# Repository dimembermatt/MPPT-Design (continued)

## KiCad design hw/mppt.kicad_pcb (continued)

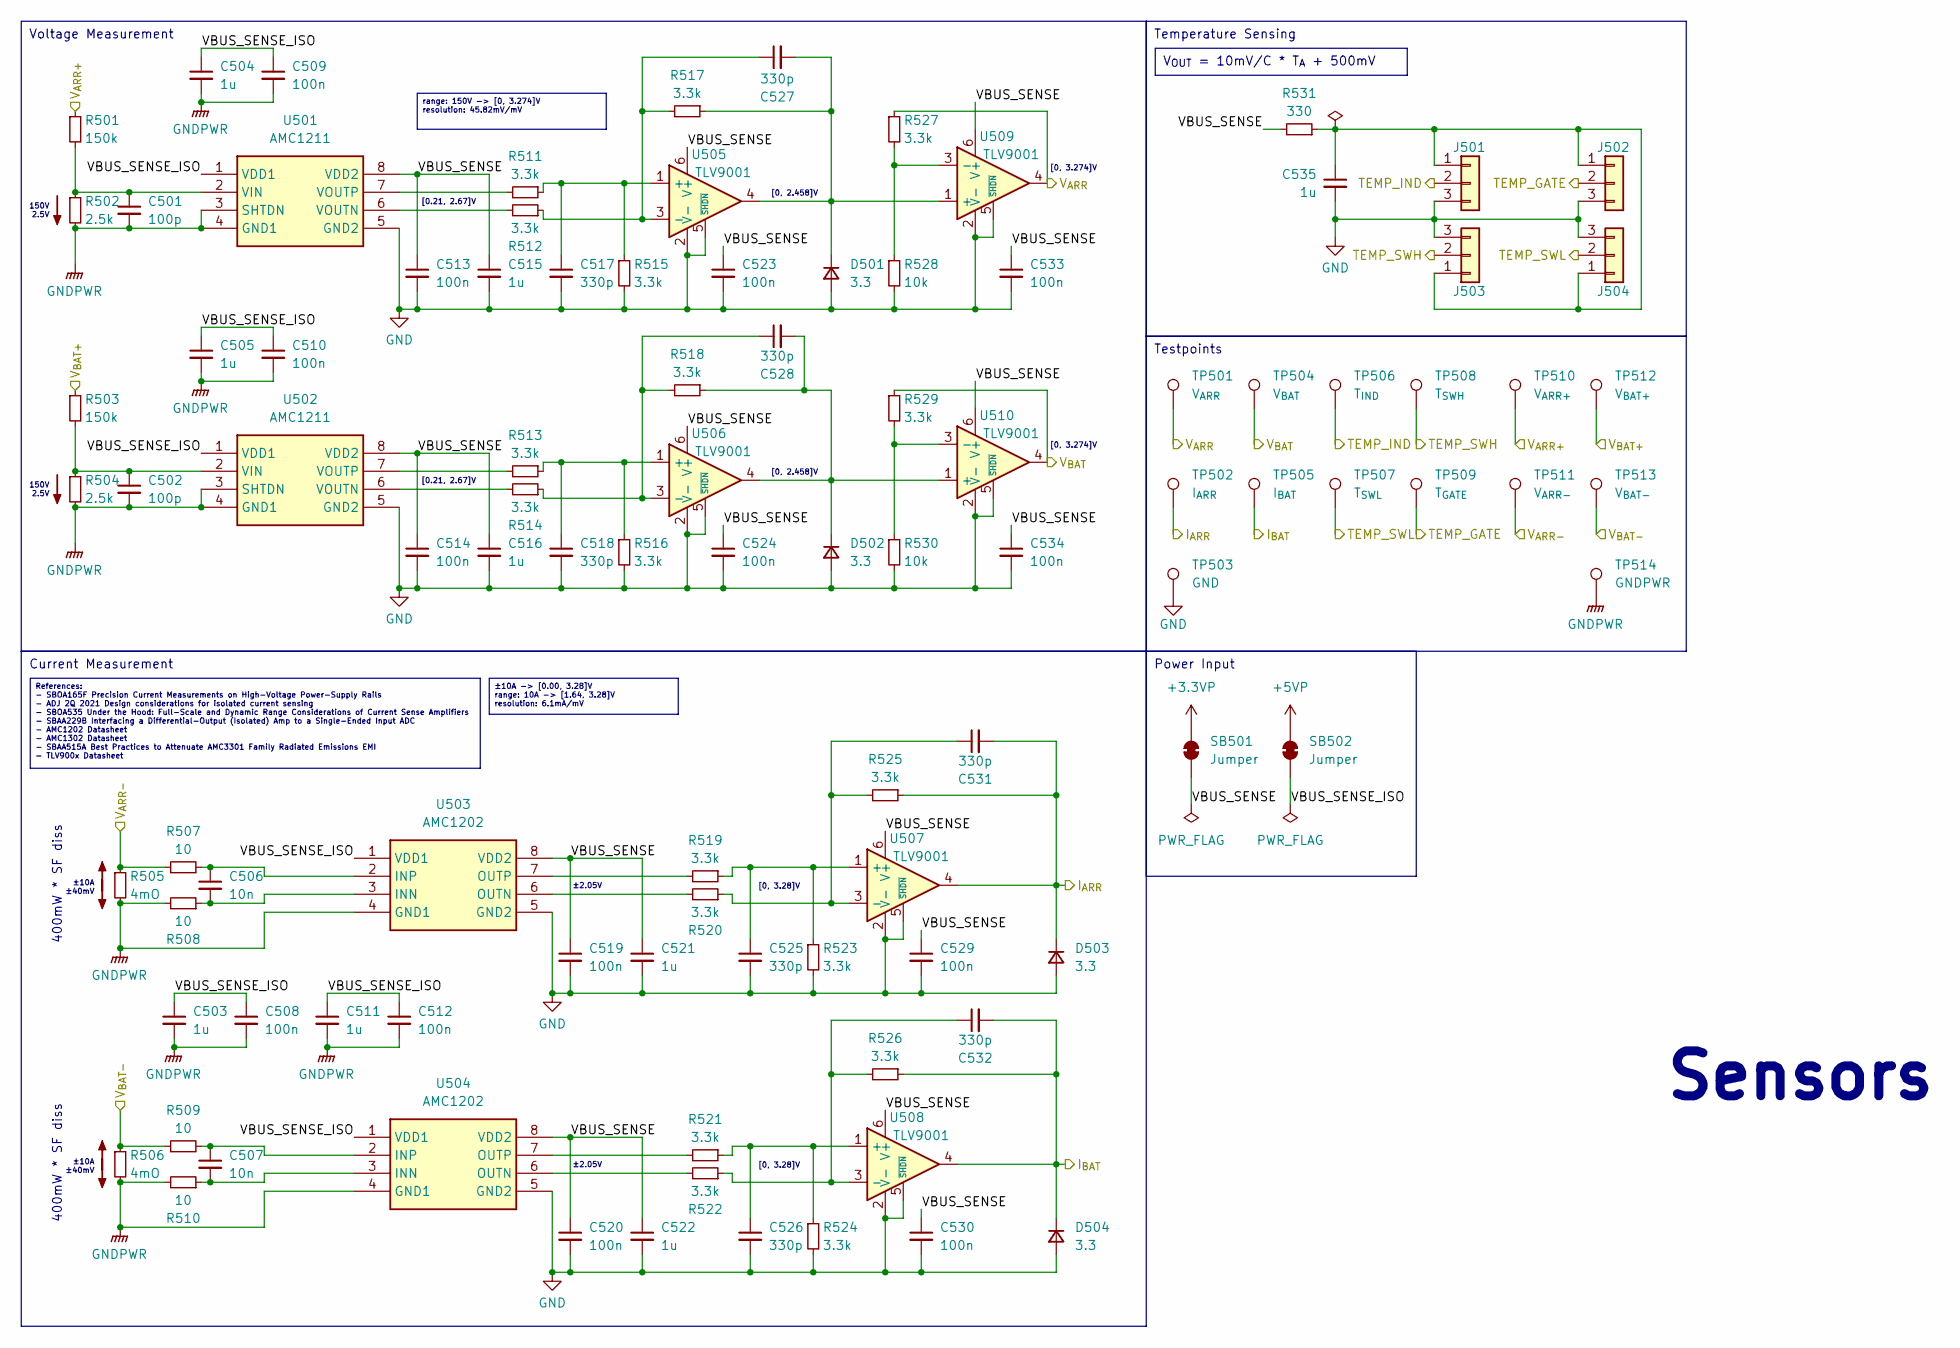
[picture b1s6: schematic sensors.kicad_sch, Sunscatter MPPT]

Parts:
C501, C502: 100p; R_0402_1005Metric; LCSC Part # C472445
C503, C504, C505, C511, C515, C516, C521, C522, C535: 1u; R_0402_1005Metric; LCSC Part # C307454
C506, C507: 10n; R_0402_1005Metric; LCSC Part # C307330
C508, C509, C510, C512, C513, C514, C519, C520, C523, C524, C529, C530, C533, C534: 100n; R_0402_1005Metric; LCSC Part # C307331
C517, C518, C525, C526, C527, C528, C531, C532: 330p; R_0402_1005Metric; LCSC Part # C307432
D501, D502, D503, D504: 3.3; D_SOD-123
J501, J502, J503, J504: Conn_01x03; JST_PH_B3B-PH-K_1x03_P2.00mm_Vertical
R501, R503: 150k; R_0805_2012Metric; LCSC Part # C17470
R502, R504: 2.5k; R_0805_2012Metric; LCSC Part # C5713447
R505, R506: 4mO; R_2512_6332Metric; LCSC Part # C2941090
R507, R508, R509, R510: 10; R_0402_1005Metric; LCSC Part # C25077
R511, R512, R513, R514, R515, R516, R517, R518, R519, R520, R521, R522, R523, R524, R525, R526, R527, R529: 3.3k; R_0402_1005Metric; LCSC Part # C25890
R528, R530: 10k; R_0402_1005Metric; LCSC Part # C25744
R531: 330; R_0402_1005Metric; LCSC Part # C25105
SB501, SB502: Jumper; SolderJumper-2_P1.3mm_Open_TrianglePad1.0x1.5mm
TP501: V_{ARR}; TestPoint_Pad_D1.5mm
TP502: I_{ARR}; TestPoint_Pad_D1.5mm
TP503: GND; TestPoint_Pad_D1.5mm
TP504: V_{BAT}; TestPoint_Pad_D1.5mm
TP505: I_{BAT}; TestPoint_Pad_D1.5mm
TP506: T_{IND}; TestPoint_Pad_D1.5mm
TP507: T_{SWL}; TestPoint_Pad_D1.5mm
TP508: T_{SWH}; TestPoint_Pad_D1.5mm
TP509: T_{GATE}; TestPoint_Pad_D1.5mm
TP510: V_{ARR+}; TestPoint_Pad_D1.5mm
TP511: V_{ARR-}; TestPoint_Pad_D1.5mm
TP512: V_{BAT+}; TestPoint_Pad_D1.5mm
TP513: V_{BAT-}; TestPoint_Pad_D1.5mm
TP514: GNDPWR; TestPoint_Pad_D1.5mm
U501, U502: AMC1211; ti_AMC1211_DWV
U503, U504: AMC1202; ti_AMC1202_DWV
U505, U506, U507, U508, U509, U510: TLV9001; SOT-363_SC-70-6

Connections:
+3.3VP: SB501.2 (B); also elsewhere on the board
+5VP: SB502.2 (B); also elsewhere on the board
/I_{ARR}: C531.2, D503.1 (K), R525.1, TP502.1, U507.4; also elsewhere on the board
/I_{BAT}: C532.2, D504.1 (K), R526.1, TP505.1, U508.4; also elsewhere on the board
/TEMP_GATE: J502.2, TP509.1; also elsewhere on the board
/TEMP_IND: J501.2, TP506.1; also elsewhere on the board
/TEMP_SWH: J503.2, TP508.1; also elsewhere on the board
/TEMP_SWL: J504.2, TP507.1; also elsewhere on the board
/V_{ARR+}: R501.1, TP510.1; also elsewhere on the board
/V_{ARR-}: R505.1, R507.1, TP511.1; also elsewhere on the board
/V_{ARR}: R527.1, TP501.1, U509.4; also elsewhere on the board
/V_{BAT+}: R503.1, TP512.1; also elsewhere on the board
/V_{BAT-}: R506.1, R509.1, TP513.1; also elsewhere on the board
/V_{BAT}: R529.1, TP504.1, U510.4; also elsewhere on the board
/sensors/VBUS_SENSE: C513.1, C514.1, C515.1, C516.1, C519.1, C520.1, C521.1, C522.1, C523.1, C524.1, C529.1, C530.1, C533.1, C534.1, R531.2, SB501.1 (A), U501.8 (VDD2), U502.8 (VDD2), U503.8 (VDD2), U504.8 (VDD2), U505.6 (V+), U506.6 (V+), U507.6 (V+), U508.6 (V+), U509.6 (V+), U510.6 (V+)
/sensors/VBUS_SENSE_ISO: C503.1, C504.1, C505.1, C508.1, C509.1, C510.1, C511.1, C512.1, SB502.1 (A), U501.1 (VDD1), U502.1 (VDD1), U503.1 (VDD1), U504.1 (VDD1)
GND: C513.2, C514.2, C515.2, C516.2, C517.2, C518.2, C519.2, C520.2, C521.2, C522.2, C523.2, C524.2, C525.2, C526.2, C529.2, C530.2, C533.2, C534.2, C535.2, D501.2 (A), D502.2 (A), D503.2 (A), D504.2 (A), J501.3, J502.3, J503.3, J504.3, R515.2, R516.2, R523.2, R524.2, R528.2, R530.2, TP503.1, U501.5 (GND2), U502.5 (GND2), U503.5 (GND2), U504.5 (GND2), U505.2 (V-), U505.5 (~SHDN), U506.2 (V-), U506.5 (~SHDN), U507.2 (V-), U507.5 (~SHDN), U508.2 (V-), U508.5 (~SHDN), U509.2 (V-), U509.5 (~SHDN), U510.2 (V-), U510.5 (~SHDN); also elsewhere on the board
GNDPWR: C501.2, C502.2, C503.2, C504.2, C505.2, C508.2, C509.2, C510.2, C511.2, C512.2, R502.2, R504.2, R505.2, R506.2, R508.2, R510.2, TP514.1, U501.3 (SHTDN), U501.4 (GND1), U502.3 (SHTDN), U502.4 (GND1), U503.4 (GND1), U504.4 (GND1); also elsewhere on the board
unnamed: C527.2, D501.1 (K), R517.1, U505.4, U509.1 (+)
unnamed: C528.2, D502.1 (K), R518.1, U506.4, U510.1 (+)
unnamed: C535.1, J501.1, J502.1, J503.1, J504.1, R531.1
unnamed: C501.1, R501.2, R502.1, U501.2 (VIN)
unnamed: R512.2, U501.6 (VOUTN)
unnamed: R511.2, U501.7 (VOUTP)
unnamed: C502.1, R503.2, R504.1, U502.2 (VIN)
unnamed: R514.2, U502.6 (VOUTN)
unnamed: R513.2, U502.7 (VOUTP)
unnamed: C506.2, R508.1, U503.3 (INN)
unnamed: C506.1, R507.2, U503.2 (INP)
unnamed: R520.2, U503.6 (OUTN)
unnamed: R519.2, U503.7 (OUTP)
unnamed: C507.2, R510.1, U504.3 (INN)
unnamed: C507.1, R509.2, U504.2 (INP)
unnamed: R522.2, U504.6 (OUTN)
unnamed: R521.2, U504.7 (OUTP)
unnamed: C517.1, R511.1, R515.1, U505.1 (+)
unnamed: C527.1, R512.1, R517.2, U505.3 (-)
unnamed: C518.1, R513.1, R516.1, U506.1 (+)
unnamed: C528.1, R514.1, R518.2, U506.3 (-)
unnamed: C525.1, R519.1, R523.1, U507.1 (+)
unnamed: C531.1, R520.1, R525.2, U507.3 (-)
unnamed: C526.1, R521.1, R524.1, U508.1 (+)
unnamed: C532.1, R522.1, R526.2, U508.3 (-)
unnamed: R527.2, R528.1, U509.3 (-)
unnamed: R529.2, R530.1, U510.3 (-)

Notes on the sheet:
References: - SBOA165F Precision Current Measurements on High-Voltage Power-Supply Rails - ADJ 2Q 2021 Design considerations for isolated current sensing - SBOA535 Under the Hood: Full-Scale and Dynamic Range Considerations of Current Sense Amplifiers - SBAA229B Interfacing a Differential-Output (I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
V_{OUT} = 10mV/C * T_{A} + 500mV
Temperature Sensing
range: 150V -> [0, 3.274]V resolution: 45.82mV/mV
Current Measurement
Power Input
±10A -> [0.00, 3.28]V range: 10A -> [1.64, 3.28]V resolution: 6.1mA/mV
Testpoints
Voltage Measurement
[0.21, 2.67]V
150V 2.5V
[0, 3.28]V
[0, 2.458]V
±2.05V
[0, 3.274]V
Sensors
±10A ±40mV
400mW * SF diss

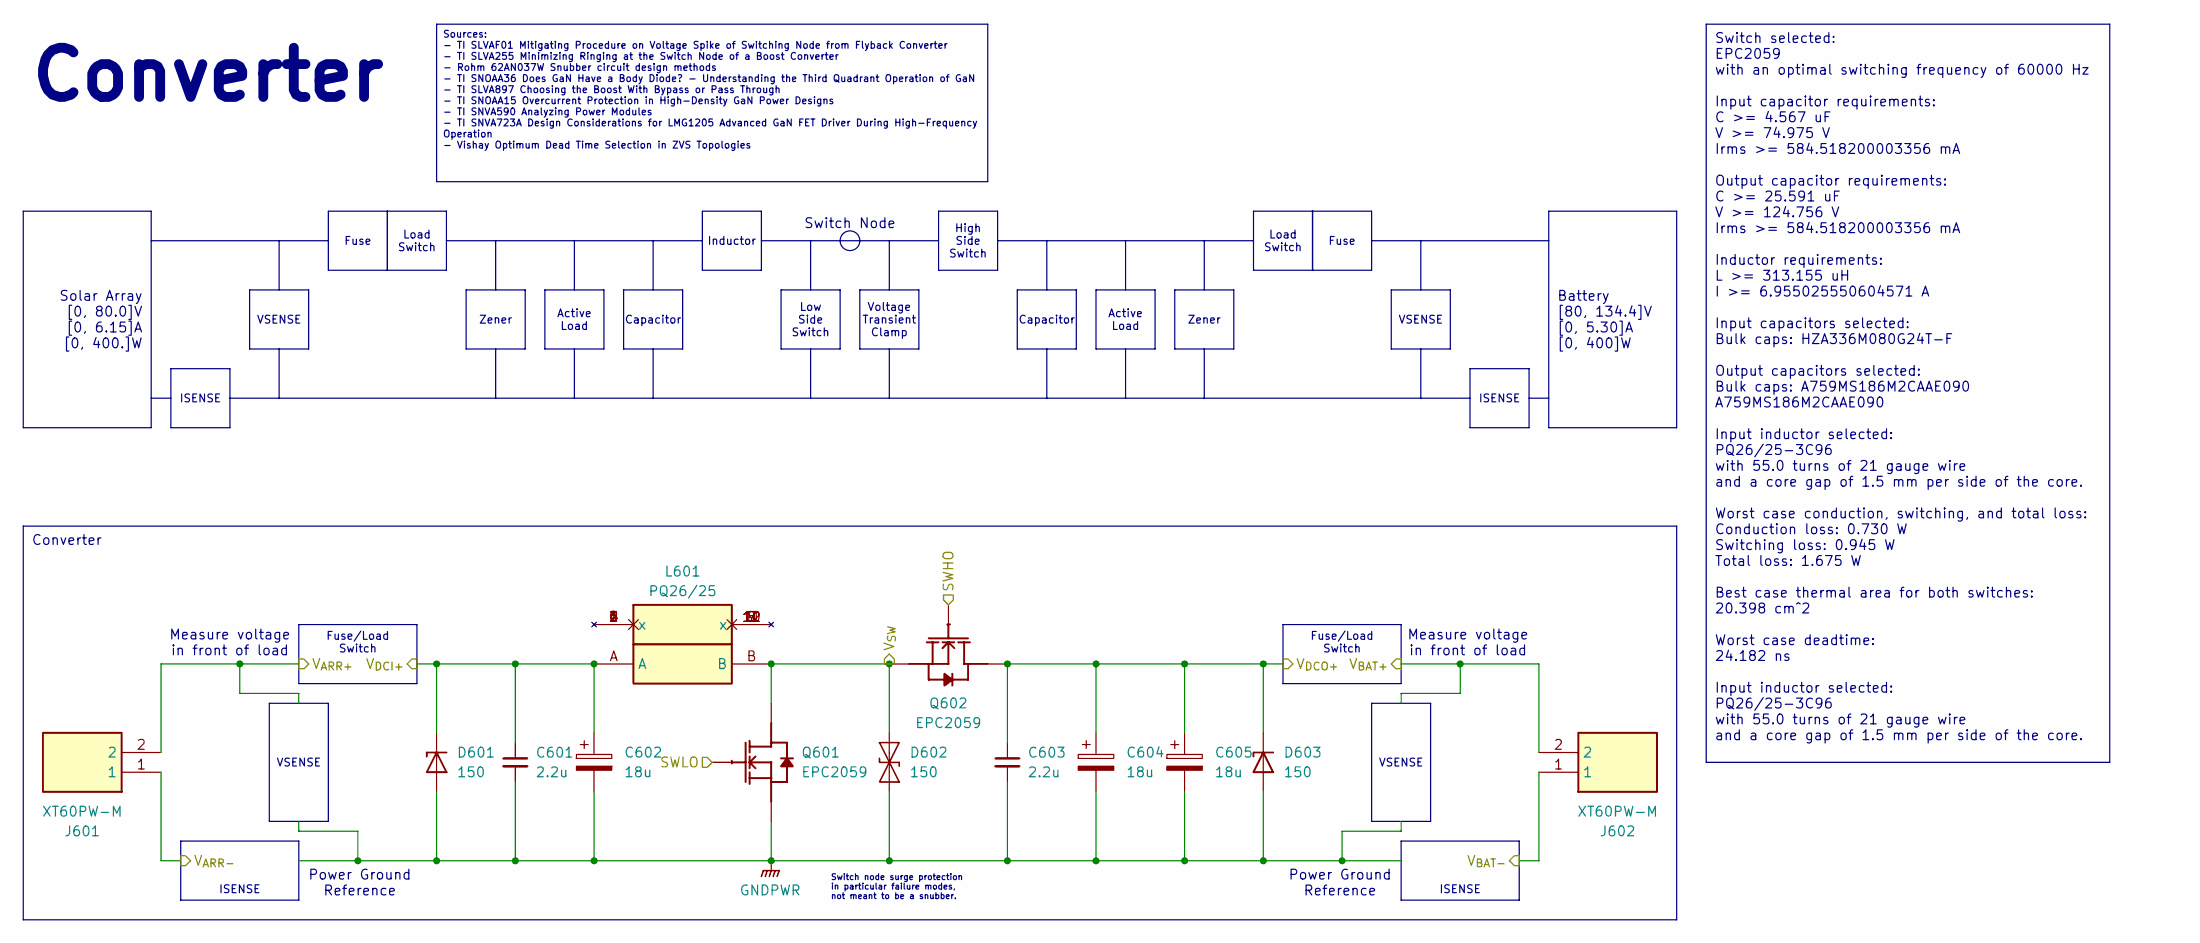
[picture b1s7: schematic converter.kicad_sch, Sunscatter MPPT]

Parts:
C601, C603: 2.2u; C_2220_5750Metric_Pad1.97x5.40mm_HandSolder
C602, C604, C605: 18u; C_Radial_D10.0mm_H16.0mm_P5.00mm
D601, D602, D603: 150; D_SMA
J601, J602: XT60PW-M; amass_XT60PW_M; LCSC Part # C98732
L601: PQ26/25; ferroxcube_CSV-PQ26_25-1S-12P-ZF
Q601, Q602: EPC2059; epc_EPC2059

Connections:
/SWHO: Q602.1 (G); also elsewhere on the board
/SWLO: Q601.1 (G); also elsewhere on the board
/V_{ARR+}: J601.2; also elsewhere on the board
/V_{ARR-}: J601.1; also elsewhere on the board
/V_{BAT+}: J602.2; also elsewhere on the board
/V_{BAT-}: J602.1; also elsewhere on the board
/V_{DCI+}: C601.1, C602.1, D601.1 (K), L601.A; also elsewhere on the board
/V_{DCO+}: C603.1, C604.1, C605.1, D603.1 (K), Q602.3 (D), Q602.5 (D); also elsewhere on the board
/V_{SW}: D602.2 (A2), L601.B, Q601.3 (D), Q601.5 (D), Q602.2 (S), Q602.4 (S), Q602.6 (S); also elsewhere on the board
GNDPWR: C601.2, C602.2, C603.2, C604.2, C605.2, D601.2 (A), D602.1 (A1), D603.2 (A), Q601.2 (S), Q601.4 (S), Q601.6 (S); also elsewhere on the board

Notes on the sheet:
Voltage Transient Clamp
Zener
VSENSE
Capacitor
ISENSE
Fuse/Load Switch
Low Side Switch
Converter
Solar Array [0, 80.0]V [0, 6.15]A [0, 400.]W
High Side Switch
Switch selected: EPC2059 with an optimal switching frequency of 60000 Hz Input capacitor requirements: C >= 4.567 uF V >= 74.975 V Irms >= 584.518200003356 mA Output capacitor requirements: C >= 25.591 uF V >= 124.756 V Irms >= 584.518200003356 mA Inductor requirements: L >= 313.155 uH I >= 6.95502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
Load Switch
Fuse
Active Load
Sources: - TI SLVAF01 Mitigating Procedure on Voltage Spike of Switching Node from Flyback Converter - TI SLVA255 Minimizing Ringing at the Switch Node of a Boost Converter - Rohm 62AN037W Snubber circuit design methods - TI SNOAA36 Does GaN Have a Body Diode? - Understanding the Third Quadrant Ope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
Inductor
Battery [80, 134.4]V [0, 5.30]A [0, 400]W
Switch node surge protection in particular failure modes, not meant to be a snubber.
Measure voltage in front of load
Switch Node
Power Ground Reference

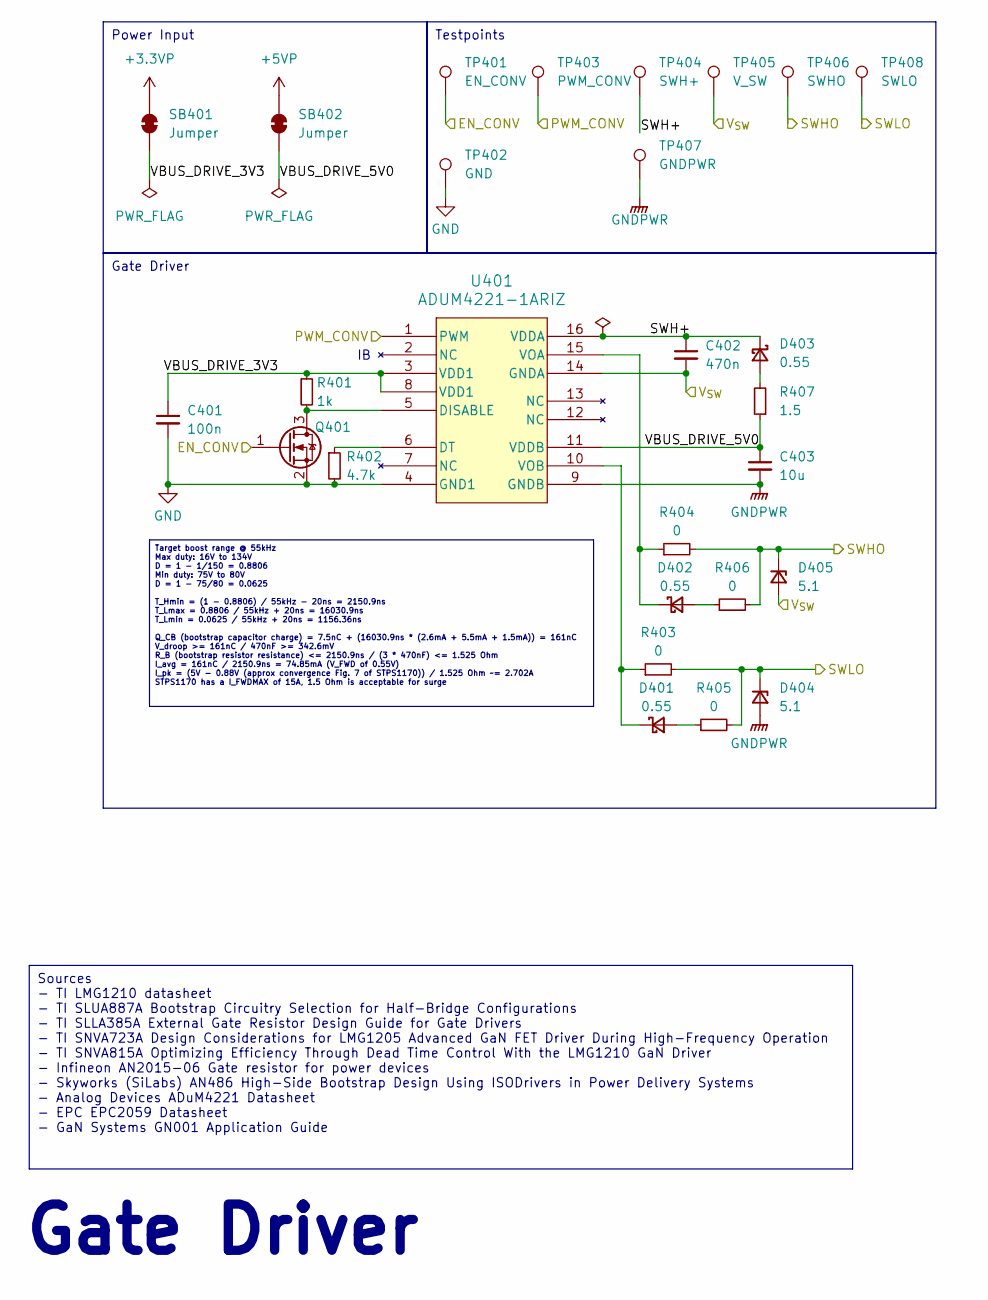
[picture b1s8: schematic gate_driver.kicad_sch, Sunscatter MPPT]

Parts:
C401: 100n; R_0402_1005Metric; LCSC Part # C307331
C402: 470n; R_0402_1005Metric; LCSC Part # C92361
C403: 10u; R_0805_2012Metric
D401, D402, D403: 0.55; stm_STPS1170AF
D404, D405: 5.1; D_SOD-123
Q401: BSS127S; SOT-23
R401: 1k; R_0402_1005Metric; LCSC Part # C11702
R402: 4.7k; R_0402_1005Metric; LCSC Part # C25900
R403, R404, R405, R406: 0; R_0402_1005Metric
R407: 1.5; R_0402_1005Metric; LCSC Part # C270642
SB401, SB402: Jumper; SolderJumper-2_P1.3mm_Open_TrianglePad1.0x1.5mm
TP401: EN_CONV; TestPoint_Pad_D1.5mm
TP402: GND; TestPoint_Pad_D1.5mm
TP403: PWM_CONV; TestPoint_Pad_D1.5mm
TP404: SWH+; TestPoint_Pad_D1.5mm
TP405: V_SW; TestPoint_Pad_D1.5mm
TP406: SWHO; TestPoint_Pad_D1.5mm
TP407: GNDPWR; TestPoint_Pad_D1.5mm
TP408: SWLO; TestPoint_Pad_D1.5mm
U401: ADUM4221-1ARIZ; ad_ADUM5221_1ARIZ

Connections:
+3.3VP: SB401.2 (B); also elsewhere on the board
+5VP: SB402.2 (B); also elsewhere on the board
/EN_CONV: Q401.1 (G), TP401.1; also elsewhere on the board
/PWM_CONV: TP403.1, U401.1 (PWM); also elsewhere on the board
/SWHO: D405.1 (K), R404.2, R406.2, TP406.1; also elsewhere on the board
/SWLO: D404.1 (K), R403.2, R405.2, TP408.1; also elsewhere on the board
/V_{SW}: C402.2, D405.2 (A), TP405.1, U401.14 (GNDA); also elsewhere on the board
/gate_driver/SWH+: C402.1, D403.1 (K), TP404.1, U401.16 (VDDA)
/gate_driver/VBUS_DRIVE_3V3: C401.1, R401.1, SB401.1 (A), U401.3 (VDD1), U401.8 (VDD1)
/gate_driver/VBUS_DRIVE_5V0: C403.1, R407.1, SB402.1 (A), U401.11 (VDDB)
GND: C401.2, Q401.2 (S), R402.2, TP402.1, U401.4 (GND1); also elsewhere on the board
GNDPWR: C403.2, D404.2 (A), TP407.1, U401.9 (GNDB); also elsewhere on the board
unnamed: D401.2 (A), R405.1
unnamed: D401.1 (K), R403.1, U401.10 (VOB)
unnamed: D402.2 (A), R406.1
unnamed: D402.1 (K), R404.1, U401.15 (VOA)
unnamed: D403.2 (A), R407.2
unnamed: Q401.3 (D), R401.2, U401.5 (DISABLE)
unnamed: R402.1, U401.6 (DT)

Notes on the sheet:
Power Input
Gate Driver
Sources - TI LMG1210 datasheet - TI SLUA887A Bootstrap Circuitry Selection for Half-Bridge Configurations - TI SLLA385A External Gate Resistor Design Guide for Gate Drivers - TI SNVA723A Design Considerations for LMG1205 Advanced GaN FET Driver During High-Frequency Operation - TI SNVA815A Optimizi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
Target boost range @ 55kHz Max duty: 16V to 134V D = 1 - 1/150 = 0.8806 Min duty: 75V to 80V D = 1 - 75/80 = 0.0625 T_Hmin = (1 - 0.8806) / 55kHz - 20ns = 2150.9ns T_Lmax = 0.8806 / 55kHz + 20ns = 16030.9ns T_Lmin = 0.0625 / 55kHz + 20ns = 1156.36ns Q_CB (bootstrap capacitor charge) = 7.5nC + (1603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
Testpoints

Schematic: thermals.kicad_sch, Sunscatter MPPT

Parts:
C801: 22u; R_0805_2012Metric
D801: 0.5; D_SMA
H801, H802, H803, H804: M2.5; MountingHole_2.5mm
HS801: Heatsink
M801: 5V; JST_PH_B2B-PH-SM4-TB_1x02-1MP_P2.00mm_Vertical
Q801: Q_NMOS_GDS; SOT-223-3_TabPin2
R801: 1k; R_0402_1005Metric; LCSC Part # C11702
R802, R803: 330; R_0402_1005Metric; LCSC Part # C25105
SB801: Jumper; SolderJumper-2_P1.3mm_Open_TrianglePad1.0x1.5mm
TP801: FAN_PWM; TestPoint_Pad_D1.5mm
TP802: GND; TestPoint_Pad_D1.5mm
TP803: FAN_SW; TestPoint_Pad_D1.5mm

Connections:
+5V: SB801.1 (A); also elsewhere on the board
/FAN_PWM: R801.1, R802.1, TP801.1
/thermals/SW_NODE: C801.2, D801.2 (A), M801.2 (-), Q801.2 (D), TP803.1
/thermals/VBUS_FAN: C801.1, D801.1 (K), R803.1, SB801.2 (B)
GND: Q801.3 (S), R801.2, TP802.1; also elsewhere on the board
unnamed: M801.1 (+), R803.2
unnamed: Q801.1 (G), R802.2

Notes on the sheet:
Active Cooling
Testpoints
Passive Cooling
Power Input
Apply on gate driver, FETs
Hole to hole is 24mm apart
Thermals
Apply on heatsink, fan should blow inwards/downwards

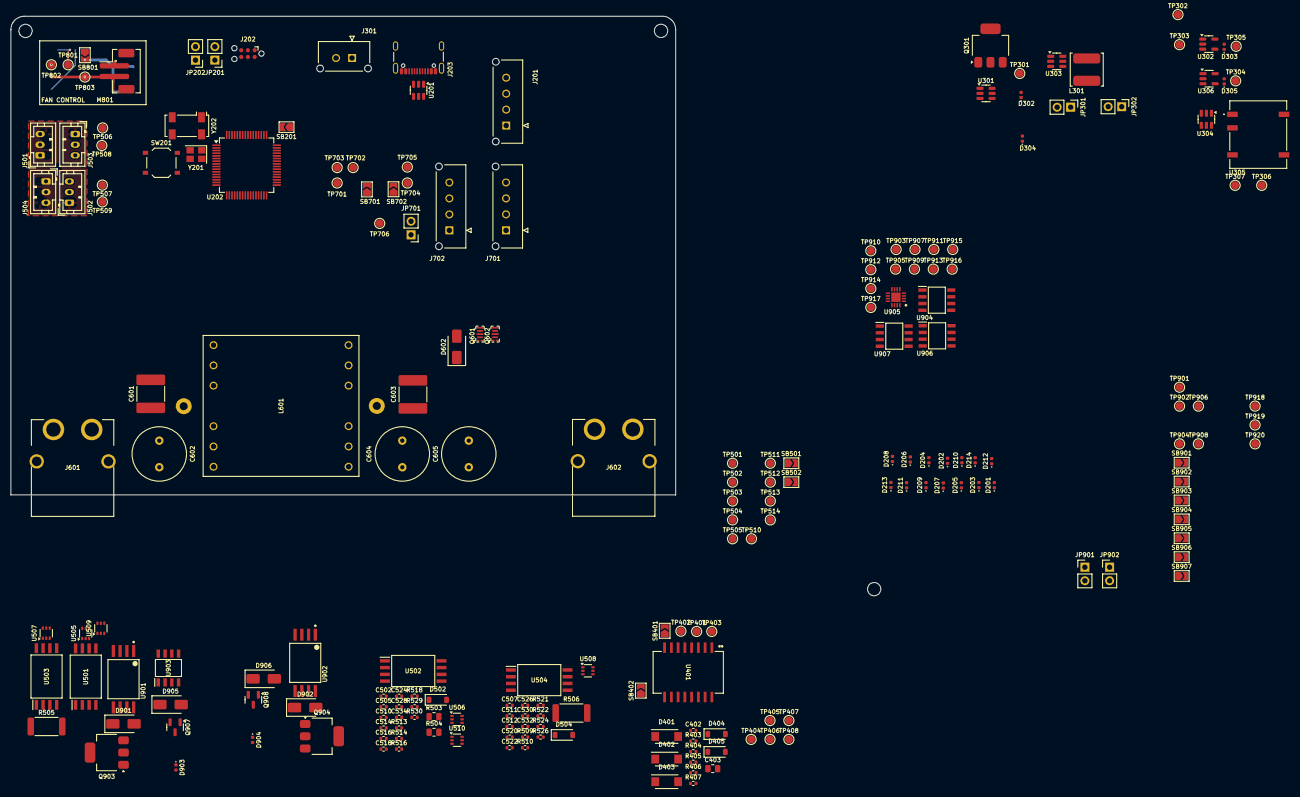
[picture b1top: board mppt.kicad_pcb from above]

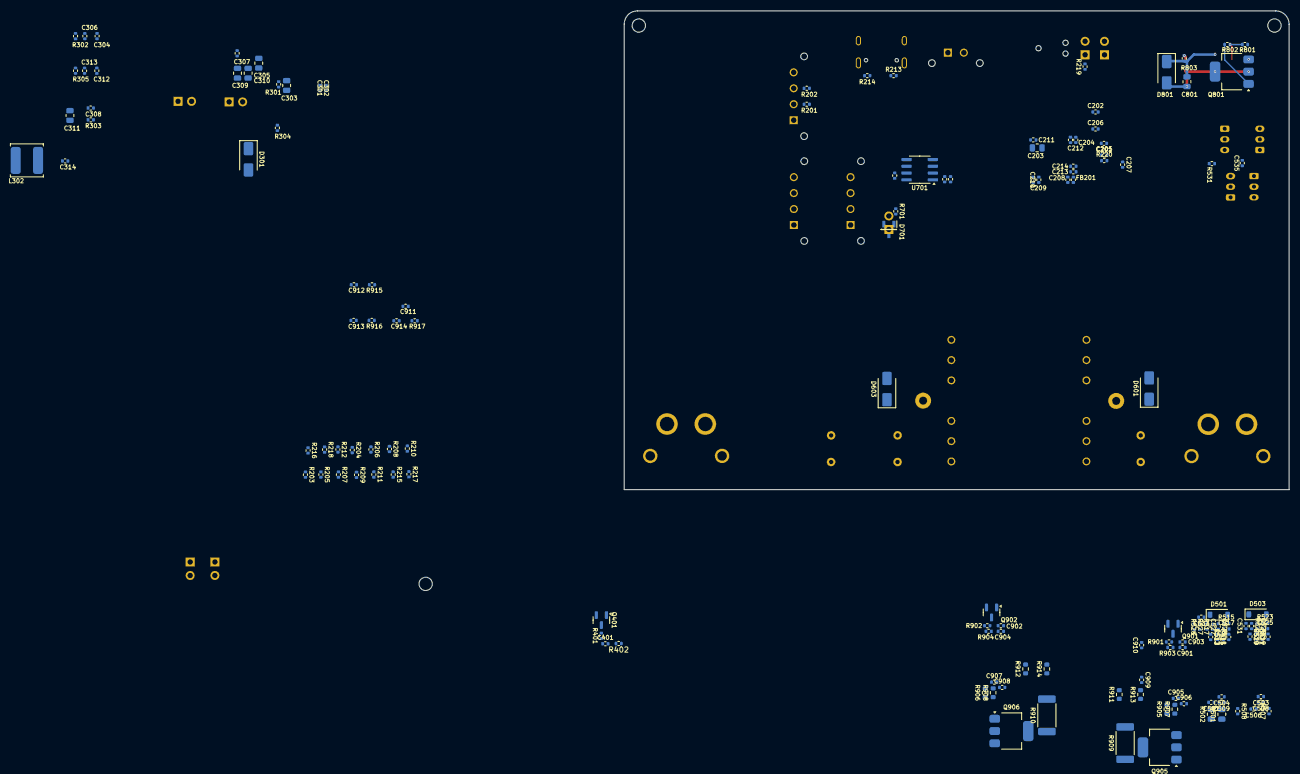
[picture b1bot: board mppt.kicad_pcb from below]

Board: 4 copper layers, 125.0 x 90.0 mm, 360 parts (144 on the bottom side), 185 nets.

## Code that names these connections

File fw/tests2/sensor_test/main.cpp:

/**
 * @file main.cpp
 * @author Matthew Yu (matthewjkyu@gmail.com)
 * @brief Sunscatter power sensor test. Verify that:
 *      - Liveliness - verify that voltage and current measurements can be taken from each set of sensors.
 *      - Replication - verify that voltage and current measurements can be taken at various operating frequencies and determine precision metrics.
 *      - Accuracy - verify that the sensors are accurate within a known range of input and output conditions, with the appropriate calibration function.
 * @version 0.1.0
 * @date 2023-09-16
 *
 * @copyright Copyright (c) 2023
 *
 * @note Pinout:
 *  - D1  | PA9  | HEARTBEAT LED
 *  - D0  | PA10 | TRACKING LED
 *  - D3  | PB0  | ERROR LED
 * 
 *  - D2  | PA12 | CAN_TX
 *  - D10 | PA11 | CAN_RX
 *
 *  - A0  | PA0  | ARR CURRENT
 *  - A1  | PA1  | ARR VOLTAGE
 *  - A5  | PA6  | BATT VOLTAGE
 *  - A6  | PA7  | BATT CURRENT
 *  - A3  | PA4  | PWM ENABLE
 *  - A4  | PA5  | PWM OUT
 * 
 * @errata PWM_OUT A4 is not PWM enabled. Solder bridge to A2 (PA_3).
 */
#include "mbed.h"
#include "Filter/MedianFilter.h"

DigitalOut led_heartbeat(D1);
DigitalOut led_tracking(D0);
DigitalOut led_error(D3);
AnalogIn arr_voltage_sensor(A1);
AnalogIn arr_current_sensor(A0);
AnalogIn batt_voltage_sensor(A5);
AnalogIn batt_current_sensor(A6);

MedianFilter arr_voltage_filter(10);
MedianFilter arr_current_filter(10);
MedianFilter batt_voltage_filter(10);
MedianFilter batt_current_filter(10);


DigitalOut pwm_enable(A3);
PwmOut pwm_out(A2);

Ticker ticker_heartbeat;
EventQueue queue(32 * EVENTS_EVENT_SIZE);

/**
 * @brief Interrupt triggered by the heartbeat ticker to call an event to send a
 * pre-formed CAN message. 
 */
void handler_heartbeat(void);

/**
 * @brief Event to measure a sensor.
 */
void event_measure_sensor(void);

/**
 * @brief Apply calibration function for the array voltage sensor.
 * 
 * @param inp Input value of ADC 0.0 - 1.0.
 * @return float Voltage, Volts.
 */
float calibrate_arr_v(float inp);

/**
 * @brief Apply calibration function for the array current sensor.
 * 
 * @param inp Input value of ADC 0.0 - 1.0.
 * @return float Voltage, Volts.
 */
float calibrate_arr_i(float inp);

/**
 * @brief Apply calibration function for the battery voltage sensor.
 * 
 * @param inp Input value of ADC 0.0 - 1.0.
 * @return float Voltage, Volts.
 */
float calibrate_batt_v(float inp);

/**
 * @brief Apply calibration function for the battery current sensor.
 * 
 * @param inp Input value of ADC 0.0 - 1.0.
 * @return float Voltage, Volts.
 */
float calibrate_batt_i(float inp);

int main()
{
    set_time(0);
    ThisThread::sleep_for(1000ms);
    printf("Power Sensor Test\n");
    
    arr_voltage_sensor.set_reference_voltage(3.321);
    arr_current_sensor.set_reference_voltage(3.321);
    batt_voltage_sensor.set_reference_voltage(3.321);
    batt_current_sensor.set_reference_voltage(3.321);

    ticker_heartbeat.attach(&handler_heartbeat, 100ms);

    led_heartbeat = 0;
    led_tracking = 0;
    led_error = 0;

    pwm_out.period(1.0 / 100000.0); // 100 kHz

    // Force HIGH
    pwm_out.write(1.0);
    pwm_enable = 1;

    led_tracking = 1;

    /**
     * Testing:
     * - V_ARR: Supply 0 - 80 V to input and compare expected (multimeter) with received.
     * - V_BATT: enable off, supply 0 - 130 V to output and compare expected with received.
     * - I_ARR, I_BATT: enable on, 100% duty to short high side switch, tie output to short current. 
     *   Supply 0 - 6 A to input and compare expected (multimeter on both sides) with received.
     * Note that there is ~1.29V drop on some conditions (enable = 0, duty = 1.0). This may be an issue.
     */

    queue.dispatch_forever();
    while(true);
}

void handler_heartbeat(void) { 
    led_heartbeat = !led_heartbeat;
    queue.call(&event_measure_sensor);
}

void event_measure_sensor(void) {
    // Measure sensor
    time_t seconds = time(NULL);

    float arr_v = calibrate_arr_v(arr_voltage_sensor.read());
    float arr_i = calibrate_arr_i(arr_current_sensor.read());
    float batt_v = calibrate_batt_v(batt_voltage_sensor.read());
    float batt_i = calibrate_batt_i(batt_current_sensor.read());

    arr_voltage_filter.addSample(arr_v);
    arr_current_filter.addSample(arr_i);
    batt_voltage_filter.addSample(batt_v);
    batt_current_filter.addSample(batt_i);

    // CSV format for later analysis.
    printf(
        "%u,%f,%f,%f,%f\n", 
        (unsigned int) seconds, 
        arr_voltage_filter.getResult(), 
        arr_current_filter.getResult(), 
        batt_voltage_filter.getResult(), 
        batt_current_filter.getResult()
    );
}

float calibrate_arr_v(float inp) {
    if (inp < 1.0) return inp * 114.021;
    else return 114.021; 
}

float calibrate_arr_i(float inp) {
    if (inp < 1.0) return inp * 8.3025;
    else return 8.3025;
}

float calibrate_batt_v(float inp) {
    if (inp < 1.0) return inp * 169.371;
    else return 169.371;
}

float calibrate_batt_i(float inp) {
    if (inp < 1.0) return inp * 8.3025;
    else return 8.3025;
}

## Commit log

2023-01-31 init commit
2023-02-02 commit deisgn files
2023-02-02 input fix
2023-02-02 initial sim files for kicad spice sim, freeze on design.py
2023-02-03 cleaned up design process file.
2023-02-03 fix bugs and standard inputs/output
2023-02-03 save comments for mosfet selection
2023-02-03 TODO for change
2023-02-04 generated outputs
2023-02-07 commit last run of sw
2023-02-26 working on documentation, design methmethodology, sizing, layout
2023-02-26 parts of gate driver
2023-02-27 thermal design
2023-02-27 laid out MOSFET switching loop and thermal connections
2023-02-27 made gate driver loop v1
2023-02-27 test for inductor, stuff, resizing..
2023-02-27 layout revision this one is cursed
2023-02-27 slight bom updates
2023-02-27 improved thermals of fets with internal vias, internal traces, and thermal jumpers
2023-02-28 even better thermal design, kept pours out of MOSFET pins and sswitched to 0805 thermal jumpers
2023-02-28 revision of PCB layout
2023-03-02 segregating code into design procedures
2023-03-03 Design partioning, might've gotten the parameters down, more documents
2023-03-03 notes frorom OH
2023-03-04 added Vsw test point and altered Vsw trace slightly
2023-03-04 Added proper signal TPs for Vsw, both gate signals, and PWM, added BNC connector for PWM control signal to STM analog pin, increased Vsw zone on F.cu, in.1, and in.2, reduced vias directly under fets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
2023-03-05 changed low-speed test points to through-hole standoffs, created a thermal sink area for high-side fet on B.Cu, and changed some thermal resistors to larger 1225 package where available due to lower 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
2023-03-06 rebuild schematic, passes ERC, bom completed
2023-03-06 screw locks
2023-03-06 savestate layout
2023-03-06 final layout
2023-03-06 temp for matthew to stitch
2023-03-07 via stitching
2023-03-08 production files for v0.1.0. Change cap power calc to be based off i_rms of i_pkpk, not i_pk + r_l_a
2023-03-09 update bom
2023-03-09 added TJ's and 15uF output capacitor population options
2023-03-10 fixed gate driver circuit, filleted filled zones, ensured DRC conformity regarding clearances
2023-03-13 rebuild layout w/ passing drc
2023-03-26 writing fw tests
2023-03-27 tests for the converter
2023-04-02 fixes for v0.1.1rc
2023-04-02 fastpwm import, test modifications
2023-04-02 boost test
2023-04-02 updated pid controller test with changes from boost test, we have experienced convergence :eyes:
2023-04-02 note that indicator LED pins should hook up to PWM in v0.1.1rc for dimming
2023-04-21 updated instructions for v0.2.0 - v0.5.0 development candidates.
2023-05-02 savestate
2023-05-10 v0.2.0 design automation, documentation
2023-06-26 hw changes
2023-07-17 rm dev folder which breaks linux kids
2023-07-22 v0.2.0
2023-07-22 bugfix for wrong adc pin for batt current measurements
2023-07-27 savestate, remove extraneous files
2023-08-09 v3 savestate
2023-08-12 fix for swapped xt60 connectors
2023-08-13 change inductor kg, updated inductor options, reran output
2023-08-19 regen components for ordering
2023-12-02 documentation for v0.2.0, firmware
2023-12-05 updated fw and tests, compile
2023-12-05 implementation of some local MPPT algorithms. compiles.
2023-12-10 mv output2 into v0.2.0
2024-01-12 update testing documentation and boost, sensor test fw
2024-05-03 init sch changes
2024-06-10 v0.3.0rc (v1.0.0rc) sch complete
2024-06-10 rm .lck
2024-07-01 HW sch changes, further layout progression
2024-08-19 update v0.3.0 design notes
